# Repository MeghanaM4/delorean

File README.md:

# delorean
A super cool nixie clock made with a custom PCB powered by a raspberry pi pico W.
## Why
I recently discovered nixie tubes and was like "I should totally make something with that". I wanted to make something a bit more complicated for my first go, but this clock sets me up pretty well do to some cooler stuff (and will make for a pretty awesome present).         

## Case + Board
I've been trying to get better at Inventor (people keep shaming me for using Fusion, so), and this project was a good way to ease back into it. I was also painfully reminded of how hard it is to CAD without a mouse.

## PCB
This is my 3rd PCB, and while it took a lot less time than my first, it was still a hassle to route all those nixie tubes. Pretty happy with the way it turned out, and might have to add some more silkscreen stuff to it.

## Design Process
If you want to learn how I'm making this, check out the [journal](/JOURNAL.md)

## BOM
| Item | Qty | Cost/item | Total Cost |
| ---- | --- | --------- | ---------- |
| IN-12 nixie tubes | 6 | $5.08 | $30.50 |
| K155ID1 controller chip | 6 | $1 | $6 |
| 5V to 170V boost converter | 1 | 10.50 | $10.50 |
| Raspberry Pi Pico W | 1 | $7.65 | $7.65 |
| DIP-16 chip connecter | 6 | $0.25 |$1.50 |
| Dsub pins | 100 | $0.10 | $9.58 | 
| Custom PCB from JLCPCB | 1 | ~$10 | ~$10 |
| USB Isolator | 1 | $9.99 | $9.99 | 
| USB A to C | 1 | $1.29 | $1.29 | 
| Estimated shipping |  |  | $15 |
| Total |  |  | $101.72 |

View the full BOM [here](https://docs.google.com/spreadsheets/d/1stNW1CtxRqX0r_00TOh1KZHbPOv3G7_He01Eiyjgmc0/edit?usp=sharing)

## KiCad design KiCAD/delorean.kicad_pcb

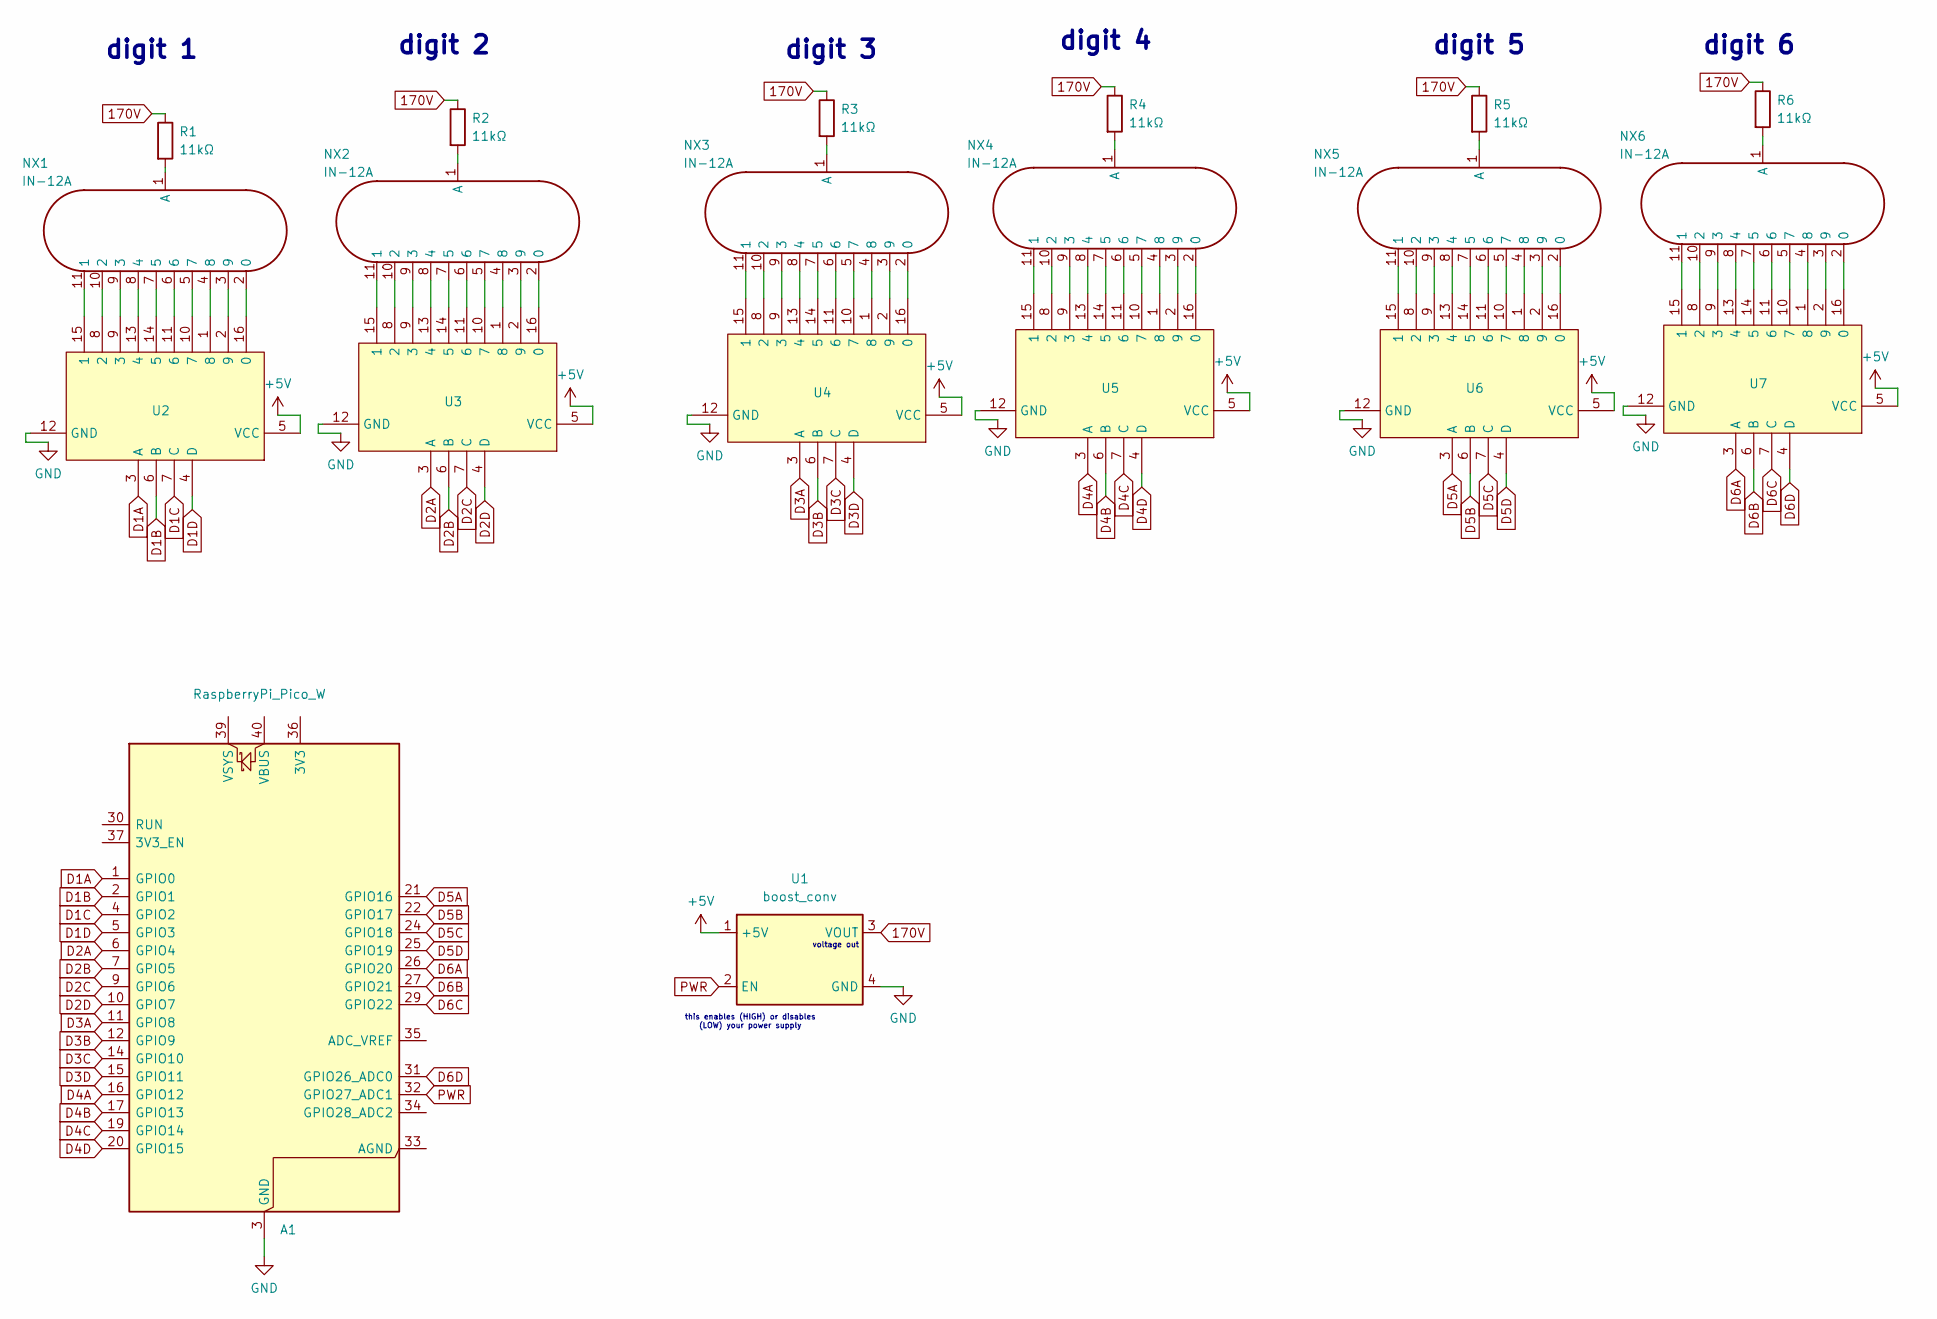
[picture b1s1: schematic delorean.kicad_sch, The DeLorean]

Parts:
A1: RaspberryPi_Pico_W; RaspberryPi_Pico_Common_THT
NX1, NX2, NX3, NX4, NX5, NX6: IN-12A; IN-12
R1, R2, R3, R4, R5, R6: 11kΩ; R_0805_2012Metric_Pad1.20x1.40mm_HandSolder
U1: boost_conv
U2, U3, U4, U5, U6, U7: K155ID1

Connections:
170V: R1.1, R2.1, R3.1, R4.1, R5.1, R6.1, U1.3 (VOUT)
+5V: U1.1 (+5V), U2.5 (VCC), U3.5 (VCC), U4.5 (VCC), U5.5 (VCC), U6.5 (VCC), U7.5 (VCC)
D1A: A1.1 (GPIO0), U2.3 (A)
D1B: A1.2 (GPIO1), U2.6 (B)
D1C: A1.4 (GPIO2), U2.7 (C)
D1D: A1.5 (GPIO3), U2.4 (D)
D2A: A1.6 (GPIO4), U3.3 (A)
D2B: A1.7 (GPIO5), U3.6 (B)
D2C: A1.9 (GPIO6), U3.7 (C)
D2D: A1.10 (GPIO7), U3.4 (D)
D3A: A1.11 (GPIO8), U4.3 (A)
D3B: A1.12 (GPIO9), U4.6 (B)
D3C: A1.14 (GPIO10), U4.7 (C)
D3D: A1.15 (GPIO11), U4.4 (D)
D4A: A1.16 (GPIO12), U5.3 (A)
D4B: A1.17 (GPIO13), U5.6 (B)
D4C: A1.19 (GPIO14), U5.7 (C)
D4D: A1.20 (GPIO15), U5.4 (D)
D5A: A1.21 (GPIO16), U6.3 (A)
D5B: A1.22 (GPIO17), U6.6 (B)
D5C: A1.24 (GPIO18), U6.7 (C)
D5D: A1.25 (GPIO19), U6.4 (D)
D6A: A1.26 (GPIO20), U7.3 (A)
D6B: A1.27 (GPIO21), U7.6 (B)
D6C: A1.29 (GPIO22), U7.7 (C)
D6D: A1.31 (GPIO26_ADC0), U7.4 (D)
GND: A1.3 (GND), A1.8 (GND), A1.13 (GND), A1.18 (GND), A1.23 (GND), A1.28 (GND), A1.38 (GND), U1.4 (GND), U2.12 (GND), U3.12 (GND), U4.12 (GND), U5.12 (GND), U6.12 (GND), U7.12 (GND)
unnamed: NX1.2 (0), U2.16 (0)
unnamed: NX1.11 (1), U2.15 (1)
unnamed: NX1.10 (2), U2.8 (2)
unnamed: NX1.9 (3), U2.9 (3)
unnamed: NX1.8 (4), U2.13 (4)
unnamed: NX1.7 (5), U2.14 (5)
unnamed: NX1.5 (7), U2.10 (7)
unnamed: NX1.4 (8), U2.1 (8)
unnamed: NX1.3 (9), U2.2 (9)
unnamed: NX1.1 (A), R1.2
unnamed: NX2.2 (0), U3.16 (0)
unnamed: NX2.11 (1), U3.15 (1)
unnamed: NX2.10 (2), U3.8 (2)
unnamed: NX2.9 (3), U3.9 (3)
unnamed: NX2.8 (4), U3.13 (4)
unnamed: NX2.7 (5), U3.14 (5)
unnamed: NX2.5 (7), U3.10 (7)
unnamed: NX2.4 (8), U3.1 (8)
unnamed: NX2.3 (9), U3.2 (9)
unnamed: NX2.1 (A), R2.2
unnamed: NX3.2 (0), U4.16 (0)
unnamed: NX3.11 (1), U4.15 (1)
unnamed: NX3.10 (2), U4.8 (2)
unnamed: NX3.9 (3), U4.9 (3)
unnamed: NX3.8 (4), U4.13 (4)
unnamed: NX3.7 (5), U4.14 (5)
unnamed: NX3.5 (7), U4.10 (7)
unnamed: NX3.4 (8), U4.1 (8)
unnamed: NX3.3 (9), U4.2 (9)
unnamed: NX3.1 (A), R3.2
unnamed: NX4.2 (0), U5.16 (0)
unnamed: NX4.11 (1), U5.15 (1)
unnamed: NX4.10 (2), U5.8 (2)
unnamed: NX4.9 (3), U5.9 (3)
unnamed: NX4.8 (4), U5.13 (4)
unnamed: NX4.7 (5), U5.14 (5)
unnamed: NX4.5 (7), U5.10 (7)
unnamed: NX4.4 (8), U5.1 (8)
unnamed: NX4.3 (9), U5.2 (9)
unnamed: NX4.1 (A), R4.2
unnamed: NX5.2 (0), U6.16 (0)
unnamed: NX5.11 (1), U6.15 (1)
unnamed: NX5.10 (2), U6.8 (2)
unnamed: NX5.9 (3), U6.9 (3)
unnamed: NX5.8 (4), U6.13 (4)
unnamed: NX5.7 (5), U6.14 (5)
unnamed: NX5.5 (7), U6.10 (7)
unnamed: NX5.4 (8), U6.1 (8)
unnamed: NX5.3 (9), U6.2 (9)
unnamed: NX5.1 (A), R5.2
unnamed: NX6.2 (0), U7.16 (0)
unnamed: NX6.11 (1), U7.15 (1)
unnamed: NX6.10 (2), U7.8 (2)
unnamed: NX6.9 (3), U7.9 (3)
unnamed: NX6.8 (4), U7.13 (4)
unnamed: NX6.7 (5), U7.14 (5)
unnamed: NX6.5 (7), U7.10 (7)
unnamed: NX6.4 (8), U7.1 (8)
unnamed: NX6.3 (9), U7.2 (9)
unnamed: NX6.1 (A), R6.2
unnamed: NX1.6, U2.11 (6)
unnamed: NX2.6, U3.11 (6)
unnamed: NX3.6, U4.11 (6)
unnamed: NX4.6, U5.11 (6)
unnamed: NX5.6, U6.11 (6)
unnamed: NX6.6, U7.11 (6)
PWR: A1.32 (GPIO27_ADC1), U1.2 (EN)

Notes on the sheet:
voltage out
digit 5
digit 3
digit 4
digit 2
digit 6
this enables (HIGH) or disables (LOW) your power supply
digit 1

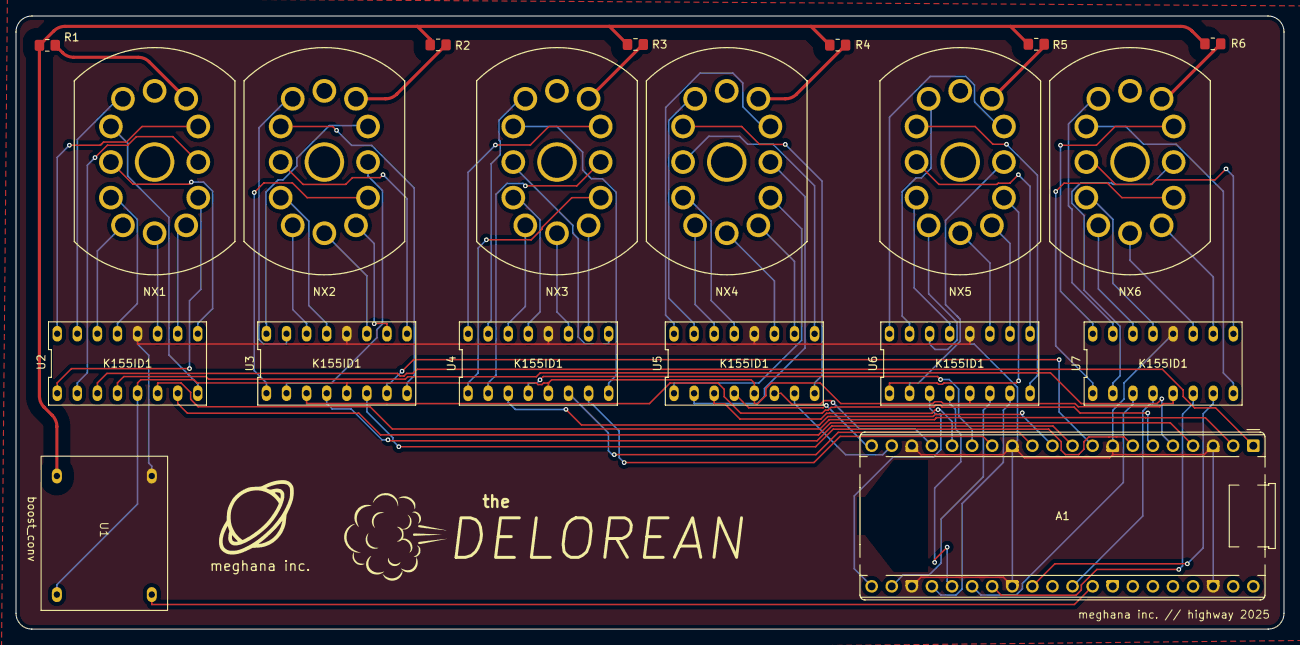
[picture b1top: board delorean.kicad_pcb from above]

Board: 2 copper layers, 160.3 x 77.5 mm, 20 parts (0 on the bottom side), 94 nets.

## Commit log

2025-06-06 started pcb
2025-06-06 add imgs
2025-06-07 updating schematic + PCB
2025-06-07 add BOM
2025-06-09 routed PCB
2025-06-09 silkscreen
2025-06-09 adding pcb img
2025-06-10 PCB update + imgs
2025-06-10 crop img
2025-06-11 case + imgs
2025-06-11 cad folder
2025-06-11 case update
2025-06-11 move
2025-06-11 whoops
2025-06-11 imgs
2025-06-12 firmware
2025-06-14 pcb update + img
2025-06-23 render stuff
2025-06-29 render
2025-12-19 Added dsub pins to BOM
